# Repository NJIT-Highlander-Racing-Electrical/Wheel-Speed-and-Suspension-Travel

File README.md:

# Wheel Speed Sensors

The 2024-2025 vehicle will be integrating sprag clutches into each of the four wheels. This allows for all four wheels to be fully locked together when power is applied, but all four wheels to be fully unlocked while coasting. There are numerous benefits to this setup that are not relevant to this project, however they present the need for individual wheel speed sensors.

These sensors provide data to the suspension subteam about how each wheel is rotating as we move through corners. Along with other vehicle data such as yaw rate, GPS position, vehicle velocity, and steering angle, suspension can get a better picture of how these sprag clutches affect vehicle performance. 

## Potential Designs

With the sprag clutches, the wheels, wheel hubs, and brake rotor all spin together. However, this rotational speed can differ from that of the axles when the clutches are in use. Thus, the sensor must detect either wheel, wheel hub, or rotor rotation.

### Gear Tooth/Ferrous Metal Target Sensor (chosen design)

These type of sensors (like the gear tooth speed sensors we have in stock -- [datasheet here](https://www.jameco.com/Jameco/Products/ProdDS/512401.pdf)) provide a digital output that tracks ferrous metal targets. Their datasheet states that they can be used for detecting holes in rotating discs, such as a brake rotor. Using the brake rotor is ideal for this situation as it does not require adding any additional hardware (such as magnets or a trigger wheel), and it actually reduces the weight of the rotor.

The ones we have in stock are no longer for sale, but [these GS100701](https://www.digikey.com/en/products/detail/zf-electronics/GS100701/280932) could work.

It seems best fit to put four holes in the edge of the rotor that will be detected by this sensor. This sensor can be mounted to a tab/bracket on the caliper, and its distance to the rotor can be adjusted using the sensor's threads/nuts. Because the rotor/caliper distances never change, we can get the sensor close enough to the rotor for accurate readings. 

Adding more than 1 hole in the edge of the rotor allows for more accurate readings. At slower speeds, there will only be a few readings per second which does not paint the most accurate picture of the true wheel speed. More than four holes could be added if the sensor/microcontroller is capable of higher polling rates.

### Permanent magnets and hall effects

If one or more permanent magnets are attached to the wheel, we can use a hall effect to detect when this magnetic field passed by. However, this means we must find a way to securely attach the magnets so that they do not fall off while spinning. Magnets also run the risk of being damaged

### Lasers/Infrared

These could be used to detect when a white stripe passes by the emitter/receiver pair (like the CVT tachometer), but dirt, mud, and other substances can cover the sensors or the sensing target.

# Suspension Travel Sensors

The 2024-2025 vehicle will also be integrating four linear suspension travel sensors. These will give an analog reading which represents the linear position of the shocks. We can then use this data to extrapolate the displacement of the wheels. We are using the LPPS-22-200 sensors from HGSI which have a 200mm stroke. They are essentially just a linear potentiometer, so they can be used with a variety of supply voltages.

## Mapping Suspension Position to Wheel Displacement

Fron two shocks have a motion ratio of 0.75, meaning that a travel 0f 0.75" in the shock would correspond to 1" of wheel displacement

# Electrical Design

These eight sensors (four wheel speed and four suspension travel) can be run to a single microcontroller located inside the vehicle, which can then transmit the data over CAN. Ideally, each wheel speed sensor reading is interrupt-based on the microcontroller so that calculations for RPM can be done as fast as possible. Suspension travel are analog so we will simply poll those for values Each sensor (at the enclosure side) has 3 pin aviation plug connectors. This prevents them from accidentally being connected to the general power/CAN bus while still maintaing our aviation plug standard. At the sensor side, each sensor uses a different, smaller in-line 3 pin connector so that the sensors themselves can be removed and replaced without removing the entire wiring harness.

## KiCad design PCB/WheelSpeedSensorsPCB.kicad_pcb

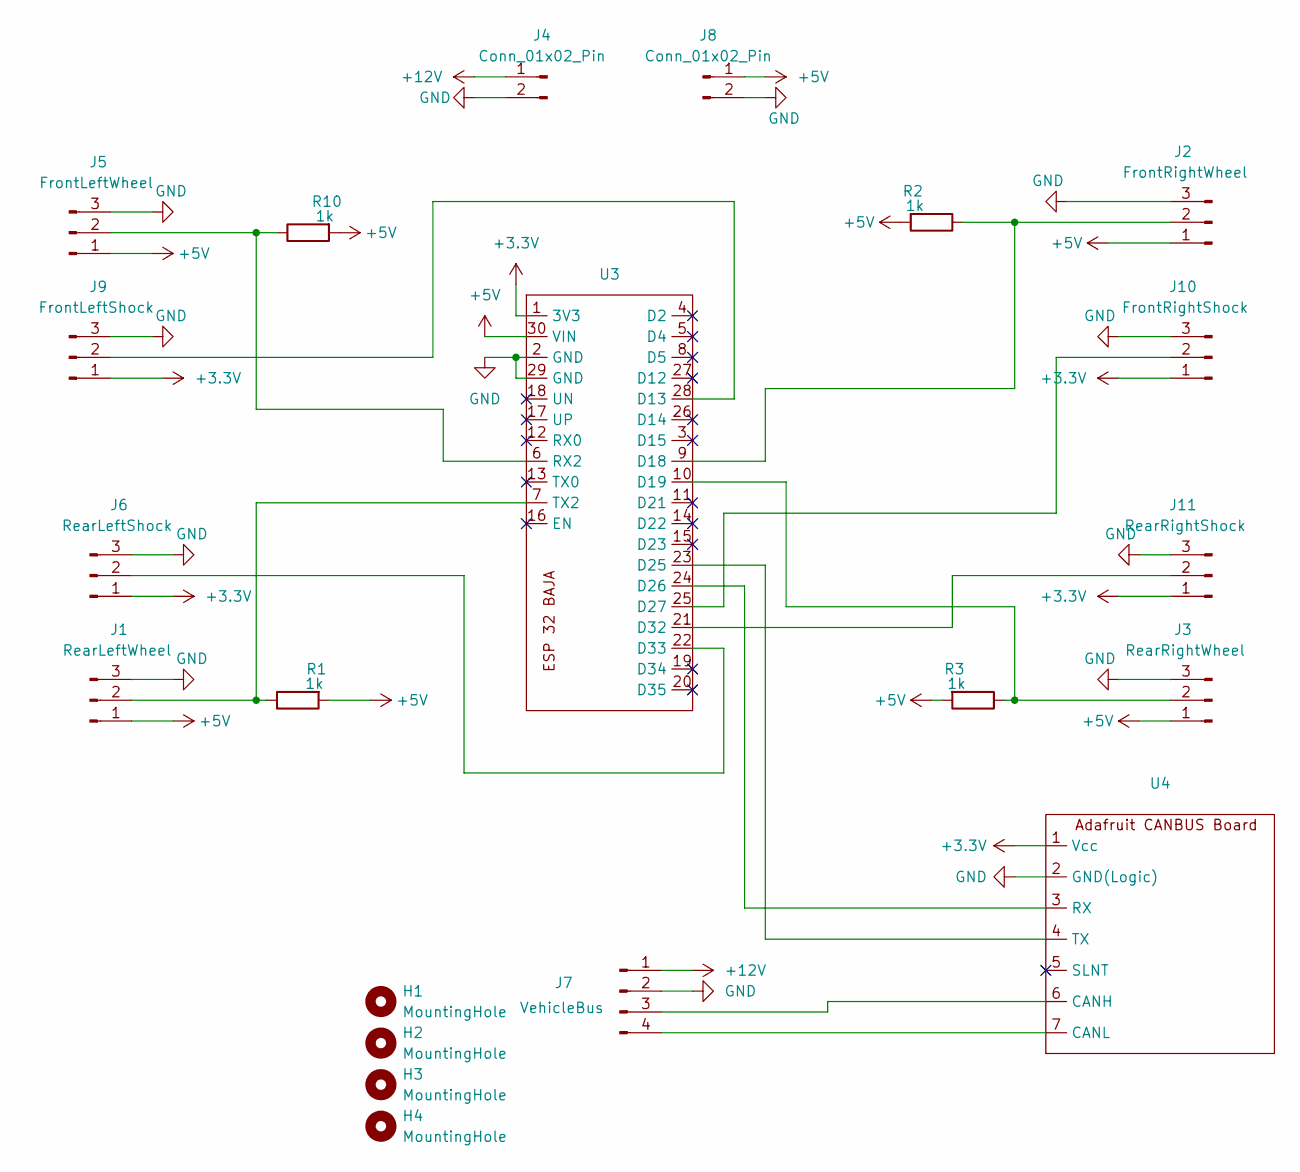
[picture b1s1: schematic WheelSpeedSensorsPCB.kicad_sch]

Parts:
H1, H2, H3, H4: MountingHole; MountingHole_4.3mm_M4
J1: RearLeftWheel; 3pin
J2: FrontRightWheel; 3pin
J3: RearRightWheel; 3pin
J4, J8: Conn_01x02_Pin; PinHeader_1x02_P2.54mm_Vertical
J5: FrontLeftWheel; 3pin
J6: RearLeftShock; 3pin
J7: VehicleBus; 4pin
J9: FrontLeftShock; 3pin
J10: FrontRightShock; 3pin
J11: RearRightShock; 3pin
R1, R2, R3, R10: 1k; R_Axial_DIN0204_L3.6mm_D1.6mm_P5.08mm_Horizontal
U3: ESP32
U4: 1x7 Connectors

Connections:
+3.3V: J6.1, J9.1, J10.1, J11.1, U3.1 (3V3), U4.1 (Vcc)
+5V: J1.1, J2.1, J3.1, J5.1, J8.1, R1.2, R2.2, R3.2, R10.2, U3.30 (VIN)
+12V: J4.1, J7.1
GND: J1.3, J2.3, J3.3, J4.2, J5.3, J6.3, J7.2, J8.2, J9.3, J10.3, J11.3, U3.2 (GND), U3.29 (GND), U4.2 (GND(Logic))
unnamed: J1.2, R1.1, U3.7 (TX2)
unnamed: J2.2, R2.1, U3.9 (D18)
unnamed: J3.2, R3.1, U3.10 (D19)
unnamed: J5.2, R10.1, U3.6 (RX2)
unnamed: J6.2, U3.22 (D33)
unnamed: J7.3, U4.6 (CANH)
unnamed: J7.4, U4.7 (CANL)
unnamed: J9.2, U3.28 (D13)
unnamed: J10.2, U3.25 (D27)
unnamed: J11.2, U3.21 (D32)
unnamed: U3.23 (D25), U4.4 (TX)
unnamed: U3.24 (D26), U4.3 (RX)

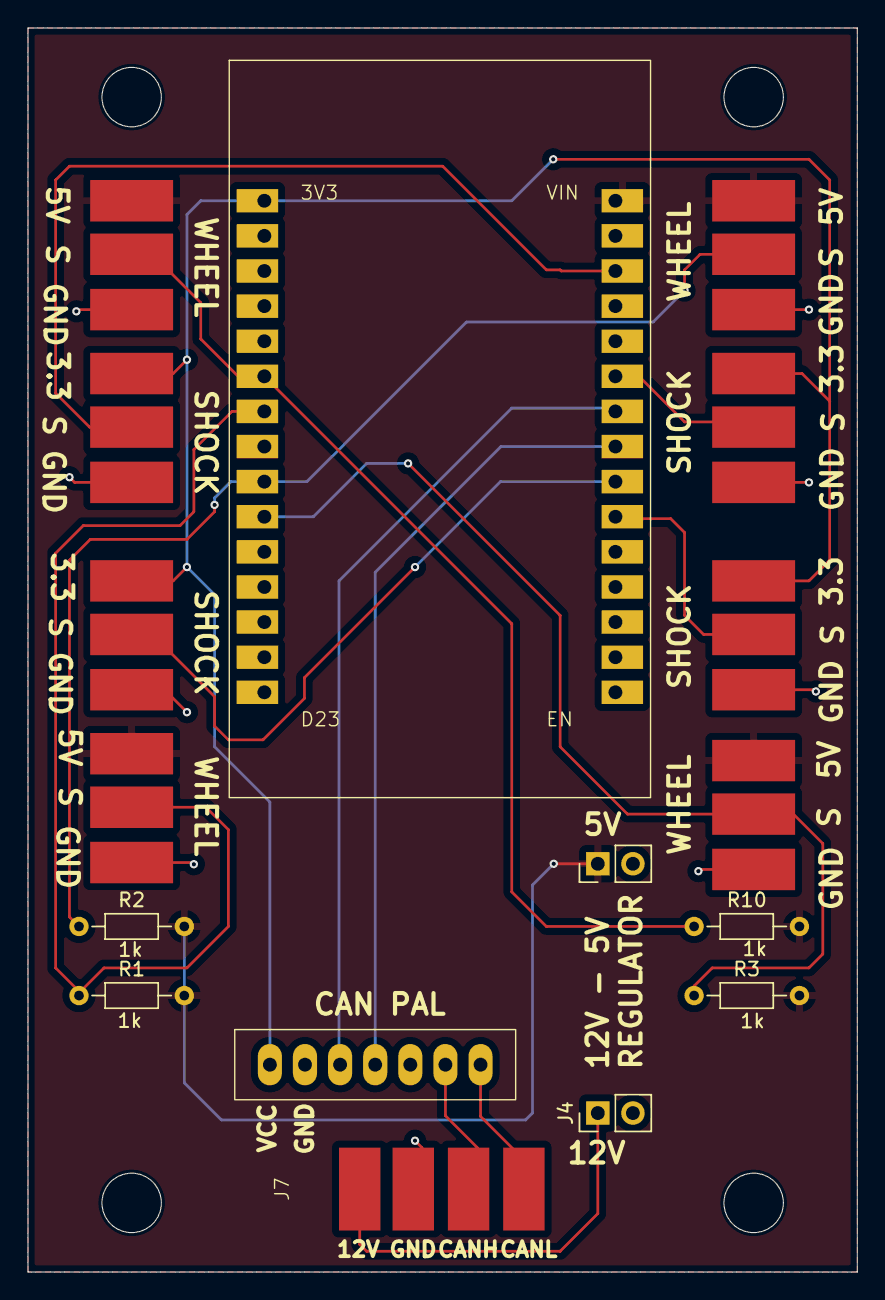
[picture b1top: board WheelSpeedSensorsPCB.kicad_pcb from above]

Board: 2 copper layers, 60.0 x 90.0 mm, 21 parts (0 on the bottom side), 16 nets.

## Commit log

2024-09-15 add link to new speed hall sensors
2024-09-16 move arduino test file inside of a proper folder
2024-09-19 Add src folder
2024-10-06 Rename WheelSpeedSensorTestSetup.ino to WheelSpeedSensorTestSetupLCD.ino
2024-10-18 Create Library123
2024-10-18 Add libraries for LCD test code
2024-10-18 Move test files for '24 car to 23-24 Archive
2024-10-18 Create Demo CodeFile123
2024-10-19 Add CAN submodule
2024-10-19 Remove Submodule
2024-10-24 Set targetsPerRevolution to 8 for front rotor
2024-11-15 Add first iteration enclosure files
2024-11-17 Update Enclosure
2024-11-18 Add first version of PCB
2024-11-20 Fix schematic/PCB to use proper CAN TX and RX pins
2024-11-20 Fix minor issue with trace to GPIO 26
2024-11-20 Add gerber and drill files for PCBWay
2024-11-21 Update PCB and GBRs to have Silkscreen
2024-11-21 Fix silkscreen mistake on vehicle bus connection
2024-11-21 Delete PCB/GRB_Files_v1_11_20_2024.zip
    Old files
2024-11-30 Major updates to structure and logic
    Add class for all four wheels
    Add spin/skid code
    Improve ISR execution
2024-11-30 Remove unused code
2024-12-05 Minor fixes to wheel revolution calculations
2024-12-05 IMPORTANT: Fix reversed 5V/GND silkscreen
    On the right side of the PCB, the 5V and GND silkscreens were reversed for the wheel speed sensors. This does not interfere with the usage of the board, but it is important to note when wiring
2024-12-05 Update footprints to better fit standard resistors
2024-12-05 Add Shock Code
2024-12-06 Update shock.h to use inch displacement
2024-12-06 Add framework for wheel displacement lookup table
2024-12-07 Fix silkscreen errors on left side shocks
2024-12-24 Update debug print statements
2024-12-29 Update 3D Models
2025-01-06 Update Subsystem to use latest CAN driver
2025-01-06 Update program to use latest CAN driver
2025-01-07 Update to latest CAN driver
2025-01-07 Activate CAN communication for subsystem
2025-01-07 Update BajaCAN.h for RTRs
    This update adds the necessary code to the BajaCAN.h file for all subsystems to receive and process any RTRs sent to them. It also adds some test code to the Wheel Speed section that will eventually 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
2025-01-08 Update to latest BajaCAN.h file
2025-01-08 Update latest BajaCAN + add checkStatus function
2025-01-08 Update latest BajaCAN
2025-02-12 Fix bug where rearLeftShock position was not being updated
2025-02-26 Add first version of 3D model
    This model includes a plastic part version that uses threaded inserts and a metal 3d printed version that has undersized holes for tapping threads
2025-02-28 Update Model Names and Update to latest design
2025-03-01 Make height shorter for Metal 3D Printing
2025-03-14 Updates
    Add new code for motion ratio, fix some convention issues
2025-03-29 Module now prints inches to CAN bus instead of analog val
2025-04-02 Update to latest CAN
2025-04-02 Update to latest BajaCAN
2025-04-24 Update variables to match new mounting orientation on vehicle
2025-04-24 Also update to latest CAN when flashing new program
2025-05-02 Several updates, see desc
    Update all Wheel RPM variables to wheel Speed MPH
    Update to latest CAN driver (also related to this RPM->MPH change)
    This driver changes what data the wheel speed sensors send
    Update rpmToMphFactor to prevent possible float rounding
2025-05-10 Update rest readings
2025-05-10 update o latest can
2025-05-10 change debug print from shock pos to wheel pos
2025-05-10 Fix bug where wheel speed was not resetting after last reading
2025-05-10 Fix bug where readings would jump to 93MPH in certain occasions
2025-05-10 Actually fix the bug
2025-05-11 Wheel Speed seems to be packet offender
    Trying to move setup CAN to see if that helps
2025-05-11 revert back to 500kbps
2025-06-08 Fix bug where motion ratio was reversed
    I was multiplying the shock position by the motion ratio to get wheel position, when in reality I should have been dividing. A motion ratio of 0.75 means that the shock will only move 0.75" for every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
2025-06-12 dont know what changed but it works now
2025-06-13 I think this works, idk
    Not even sure what i changed
2025-06-13 update rest readings for new springs
2025-06-13 Fix direction of wheel position data
2025-06-14 Fix wheel speed zeroing method
    This code updates the zeroing based on the last reading and the next expected reading time, plus a small buffer to account for a slowing down vehicle. The previous version worked based solely off a s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
2025-06-14 Comment out testing Serial prints
2025-08-02 Fixed suspenion displacement data not sending
    The parse float function reads data until a delimiter, but CAN.print does not always send a delimiter. I don't know what CAN.endpacket does. Updated to CAN.println to make it work.
    Note that the only other stuff using CAN.parseFloat is the floats from the DAS. Everything else is INTs. Nothing actually reads DAS data like acceleration or GPS, which is why we haven't seen this is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
2025-08-02 Fix serial prints taht should have been debug prints
2025-08-02 Nevermind, cant use DEBUG WHEEL Macros in .h file, just commenting them out
2025-08-02 attempt to go from println to print and print('\n'). also add short delays between messages. maybe parsefloat() is slow idk
2025-08-02 The fucking serial studio parsing was out of order... The data was sending this whole time to the console/das, but I was llooking at the wrong floats. And the wrong indices were going to the graphs f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
2025-08-02 Actually reverting to last file. Only change one thing at a time. Checking to see if serial studio works now
2025-08-02 Fixed the code. Thanks Claude
2025-08-12 Update to 1.5.0, combining all changes to all other programs
2025-09-06 Thanks clanka
2025-09-06 Change to micros for better accuracy
2025-09-07 Fix timeout bug while sending float in BajaCAN.h
2025-09-20 Increase send rate
2025-10-24 Entirely AI generated, but fuck it, it works
